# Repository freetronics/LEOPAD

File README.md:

Freetronics LeoPad
====================
Copyright 2018 Freetronics Pty Ltd  www.freetronics.com  

A USB keypad with an ATMega32u4 controller, compatible with the Arduino
Leonardo.

Features:

 * Format to match a cheap USB keypad case
 * ATmega 32u4 MCU
 * Piezo transducer for sound output
 * USB connector

You can view more details at:

  http://www.freetronics.com/leopad

INSTALLATION
------------
The design is saved as an EAGLE project. EAGLE PCB design software is
available from www.cadsoftusa.com free for non-commercial use. To use
this project download it and place the directory containing these files
into the "eagle" directory on your computer. Then open EAGLE and
navigate to the project.

CREDITS
-------
Jonathan Oxer jon@freetronics.com

DISTRIBUTION
------------
The specific terms of distribution of this project are governed by the
license referenced below.

LICENSE
-------
Licensed under the TAPR Open Hardware License (www.tapr.org/OHL).
The "license" folder within this repository also contains a copy of
this license in plain text format.

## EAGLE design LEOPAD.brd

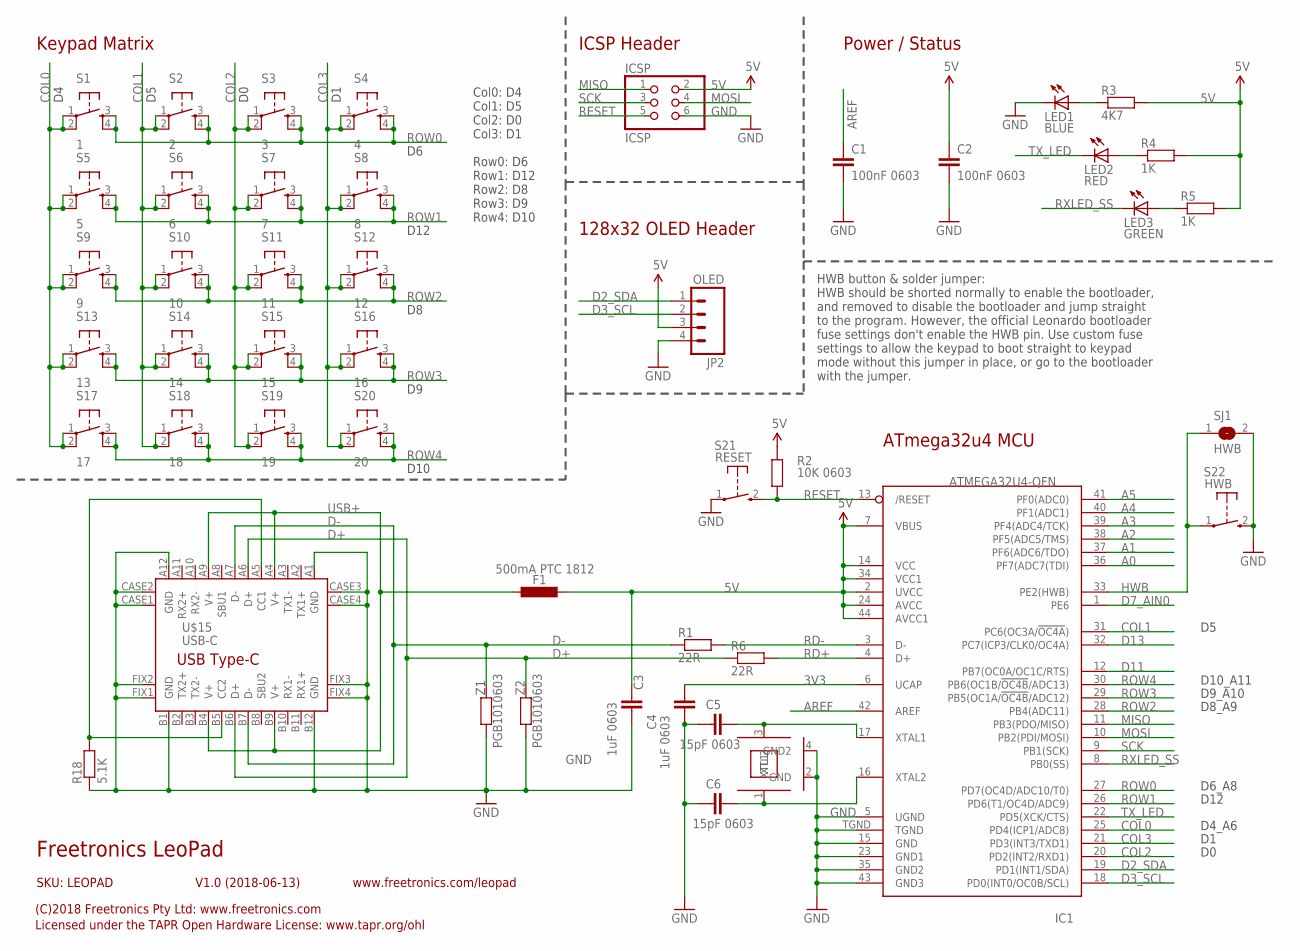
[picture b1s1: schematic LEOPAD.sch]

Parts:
C1, C2: 100nF 0603; 0603
C3, C4: 1uF 0603; 0603
C5, C6: 15pF 0603; 0603
F1: 500mA PTC 1812; L1812
IC1: ATMEGA32U4-QFN; QFN-44N
ICSP: ICSP; 2X03
JP2: OLED; 1X04
LED1: BLUE; LED-0603
LED2: RED; LED-0603
LED3: GREEN; LED-0603
R1, R6: 22R; 0603
R2: 10K 0603; 0603
R3: 4K7; 0603
R4, R5: 1K; 0603
R18: 5.1K; 0603
S1: 1; TACTILE-PTH-12MM
S2: 2; TACTILE-PTH-12MM
S3: 3; TACTILE-PTH-12MM
S4: 4; TACTILE-PTH-12MM
S5: 5; TACTILE-PTH-12MM
S6: 6; TACTILE-PTH-12MM
S7: 7; TACTILE-PTH-12MM
S8: 8; TACTILE-PTH-12MM
S9: 9; TACTILE-PTH-12MM
S10: 10; TACTILE-PTH-12MM
S11: 11; TACTILE-PTH-12MM
S12: 12; TACTILE-PTH-12MM
S13: 13; TACTILE-PTH-12MM
S14: 14; TACTILE-PTH-12MM
S15: 15; TACTILE-PTH-12MM
S16: 16; TACTILE-PTH-12MM
S17: 17; TACTILE-PTH-12MM
S18: 18; TACTILE-PTH-12MM
S19: 19; TACTILE-PTH-12MM
S20: 20; TACTILE-PTH-12MM
S21: RESET; TACTILE_SWITCH_SMD_2PIN_TINY
S22: HWB; TACTILE_SWITCH_SMD_2PIN_TINY
SJ1: HWB; SJ
U$15: USB-C; USB-C-U52A
XTL1: 16MHz; CRYSTAL-SMD-3X2
Z1, Z2: PGB1010603; 0603

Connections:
3V3: C4.2, IC1.6 (UCAP)
5V: C2.1, C3.1, F1.2, IC1.2 (UVCC), IC1.7 (VBUS), IC1.14 (VCC), IC1.24 (AVCC), IC1.34 (VCC1), IC1.44 (AVCC1), ICSP.2, JP2.3, R2.2, R3.2, R4.2, R5.2
A0: IC1.36 (PF7(ADC7(TDI))
A1: IC1.37 (PF6(ADC6/TDO))
A2: IC1.38 (PF5(ADC5/TMS))
A3: IC1.39 (PF4(ADC4/TCK))
A4: IC1.40 (PF1(ADC1))
A5: IC1.41 (PF0(ADC0))
AREF: C1.1, IC1.42 (AREF)
COL0: IC1.25 (PD4(ICP1/ADC8)), S1.1, S1.2, S5.1, S5.2, S9.1, S9.2, S13.1, S13.2, S17.1, S17.2
COL1: IC1.31 (PC6(OC3A/!OC4A!)), S2.1, S2.2, S6.1, S6.2, S10.1, S10.2, S14.1, S14.2, S18.1, S18.2
COL2: IC1.20 (PD2(INT2/RXD1)), S3.1, S3.2, S7.1, S7.2, S11.1, S11.2, S15.1, S15.2, S19.1, S19.2
COL3: IC1.21 (PD3(INT3/TXD1)), S4.1, S4.2, S8.1, S8.2, S12.1, S12.2, S16.1, S16.2, S20.1, S20.2
D2_SDA: IC1.19 (PD1(INT1/SDA)), JP2.1
D3_SCL: IC1.18 (PD0(INT0/OC0B/SCL)), JP2.2
D7_AIN0: IC1.1 (PE6)
D11: IC1.12 (PB7(OC0A/OC1C/RTS))
D13: IC1.32 (PC7(ICP3/CLK0/OC4A))
D+: R6.1, U$15.A6 (D+), U$15.B6 (D+), Z2.2
D-: R1.1, U$15.A7 (D-), U$15.B7 (D-), Z1.2
GND: C1.2, C2.2, C3.2, C4.1, C5.1, C6.1, IC1.5 (UGND), IC1.15 (GND), IC1.23 (GND1), IC1.35 (GND2), IC1.43 (GND3), IC1.TGND, ICSP.6, JP2.4, LED1.C, R18.1, S21.1, S22.2 (S), SJ1.2, U$15.A1 (GND), U$15.A12 (GND), U$15.B1 (GND), U$15.B12 (GND), U$15.CASE1 (GND), U$15.CASE2 (GND), U$15.CASE3 (GND), U$15.CASE4 (GND), U$15.FIX1 (GND), U$15.FIX2 (GND), U$15.FIX3 (GND), U$15.FIX4 (GND), XTL1.2 (GND), XTL1.4 (GND2), Z1.1, Z2.1
HWB: IC1.33 (PE2(HWB)), S22.1, SJ1.1
MISO: IC1.11 (PB3(PDO/MISO)), ICSP.1
MOSI: IC1.10 (PB2(PDI/MOSI)), ICSP.4
unnamed: LED1.A, R3.1
unnamed: LED2.A, R4.1
unnamed: LED3.A, R5.1
unnamed: C5.2, IC1.17 (XTAL1), XTL1.3 (XTL2)
unnamed: C6.2, IC1.16 (XTAL2), XTL1.1 (XTL1)
unnamed: R18.2, U$15.A5 (CC1), U$15.B5 (CC2)
RD+: IC1.4 (D+), R6.2
RD-: IC1.3 (D-), R1.2
RESET: IC1.13 (/RESET), ICSP.5, R2.1, S21.2 (S)
ROW0: IC1.27 (PD7(OC4D/ADC10/T0)), S1.3, S1.4, S2.3, S2.4, S3.3, S3.4, S4.3, S4.4
ROW1: IC1.26 (PD6(T1/OC4D/ADC9)), S5.3, S5.4, S6.3, S6.4, S7.3, S7.4, S8.3, S8.4
ROW2: IC1.28 (PB4(ADC11)), S9.3, S9.4, S10.3, S10.4, S11.3, S11.4, S12.3, S12.4
ROW3: IC1.29 (PB5(OC1A/!OC4B!/ADC12)), S13.3, S13.4, S14.3, S14.4, S15.3, S15.4, S16.3, S16.4
ROW4: IC1.30 (PB6(OC1B/!OC4B!/ADC13)), S17.3, S17.4, S18.3, S18.4, S19.3, S19.4, S20.3, S20.4
RXLED_SS: IC1.8 (PB0(SS)), LED3.C
SCK: IC1.9 (PB1(SCK)), ICSP.3
TX_LED: IC1.22 (PD5(XCK/CTS)), LED2.C
USB+: F1.1, U$15.A4 (V+), U$15.A9 (V+), U$15.B4 (V+), U$15.B9 (V+)

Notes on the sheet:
ICSP Header
ATmega32u4 MCU
HWB button & solder jumper: HWB should be shorted normally to enable the bootloader, and removed to disable the bootloader and jump straight to the program. However, the official Leonardo bootloader fuse settings don't enable the HWB pin. Use custom fuse settings to allow the keypad to boot straigh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
Freetronics LeoPad
V1.0 (2018-06-13)
SKU: LEOPAD
(C)2018 Freetronics Pty Ltd: www.freetronics.com
Licensed under the TAPR Open Hardware License: www.tapr.org/ohl
www.freetronics.com/leopad
Power / Status
D10_A11
D9_A10
D8_A9
D6_A8
D12
Col0: D4 Col1: D5 Col2: D0 Col3: D1 Row0: D6 Row1: D12 Row2: D8 Row3: D9 Row4: D10
Keypad Matrix
D4_A6
128x32 OLED Header
D10

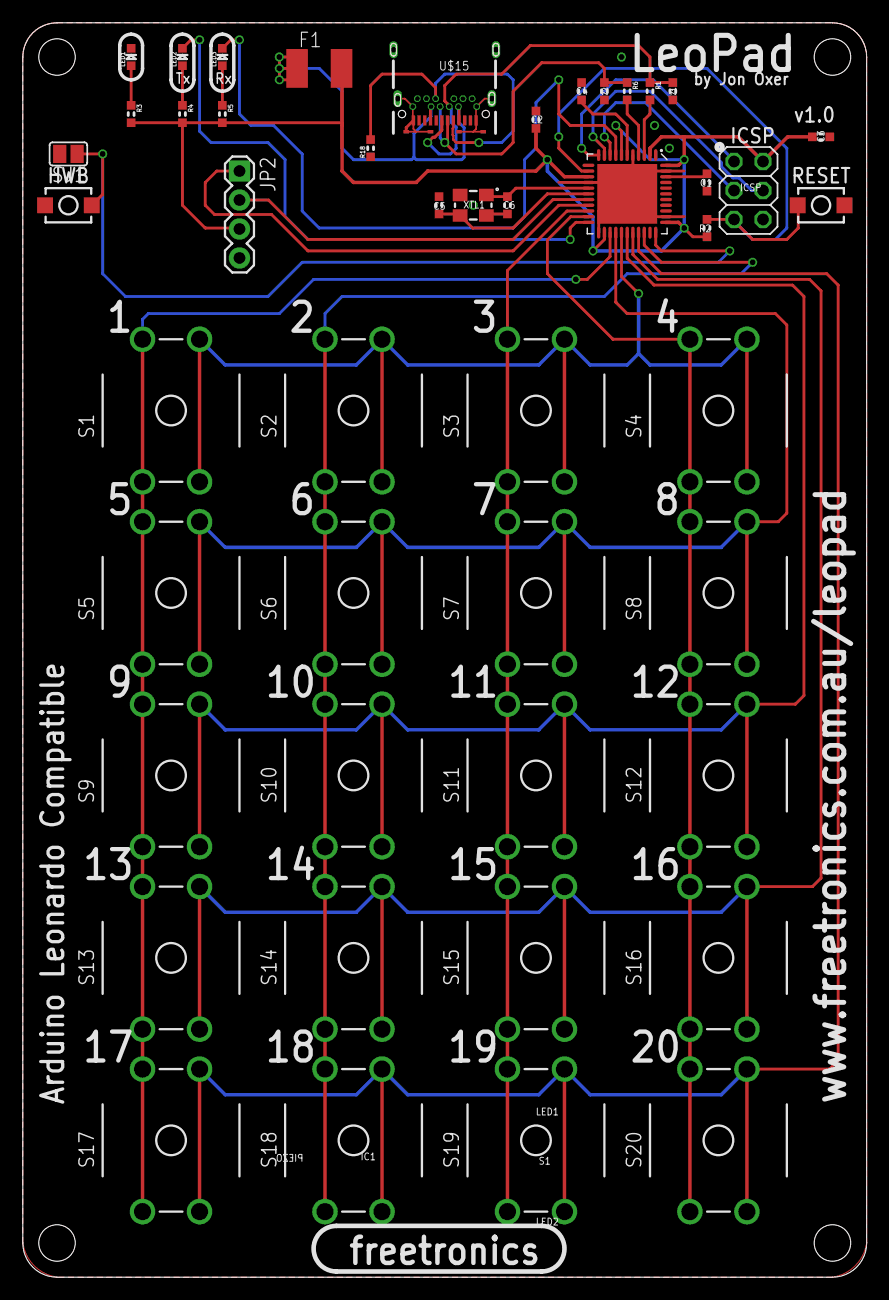
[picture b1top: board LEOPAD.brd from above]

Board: 2 copper layers, 74.0 x 110.0 mm, 47 parts (0 on the bottom side), 33 nets.

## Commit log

2018-06-06 Moved over files from LeoStick project
2018-06-27 Rework of project into keypad format
2018-06-27 Final tweaks for v1.0 release
2018-11-19 Added link to contributor license agreement as a test

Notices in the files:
LEOPAD.brd:
Released under the TAPR Open Hardware License
